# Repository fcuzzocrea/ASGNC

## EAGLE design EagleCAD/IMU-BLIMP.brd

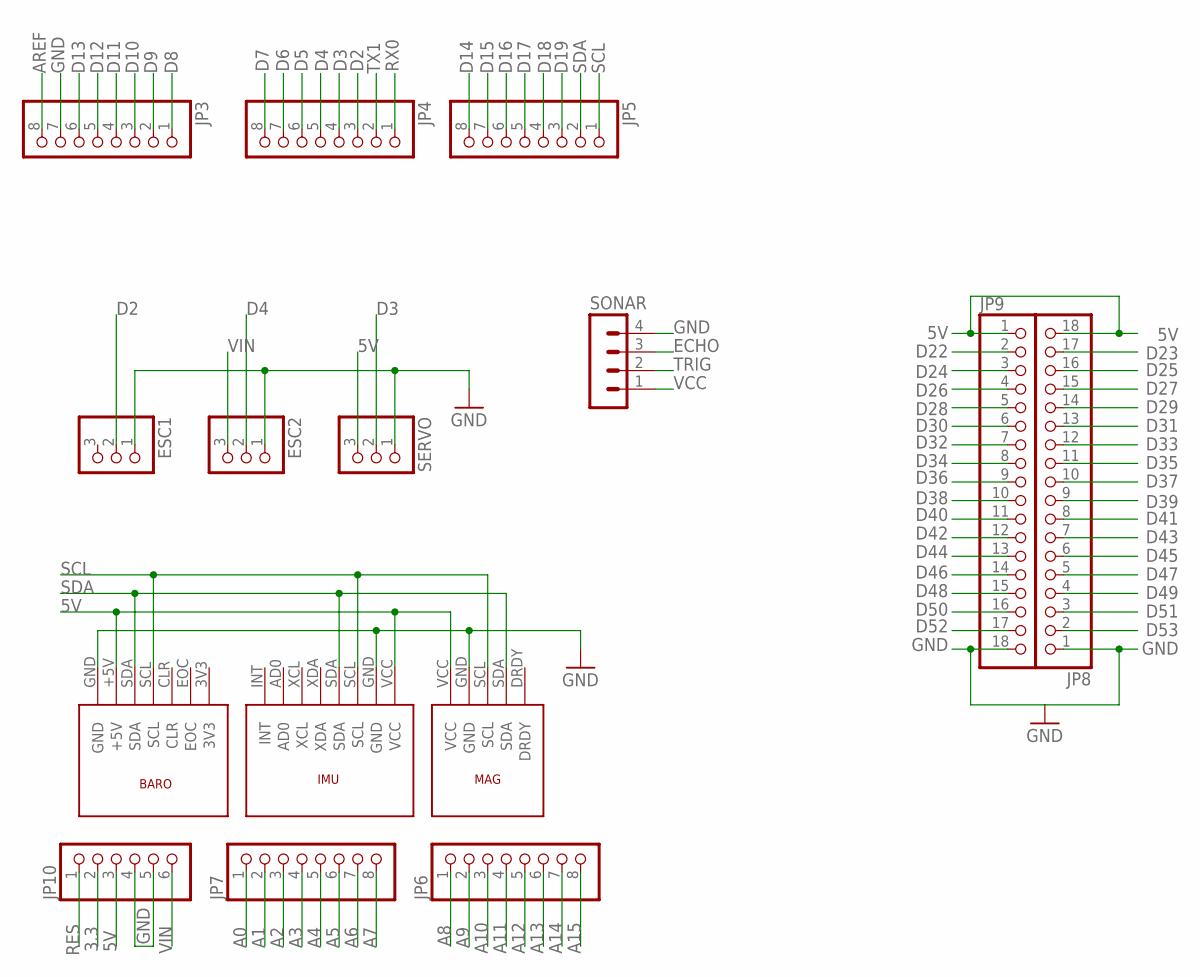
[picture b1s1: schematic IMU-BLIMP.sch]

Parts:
BARO1: BMP085
ESC1, ESC2: PINHD-1X3CB; 1X03-CLEANBIG
IMU1: MPU6050
JP3, JP4, JP5, JP6, JP7: PINHD-1X8CLEANBIG; 1X08-CLEANBIG
JP8, JP9: PINHD-1X18-BIG; 1X18-BIG
JP10: PINHD-1X6CB; 1X06-CLEANBIG
MAG1: HMC5883L
SERVO: PINHD-1X3CB; 1X03-CLEANBIG
SONAR: MA04-1

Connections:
3.3: JP10.2
5V: BARO1.+5V, IMU1.VCC, JP8.18, JP9.1, JP10.3, MAG1.VCC, SERVO.3, SONAR.1
A0: JP7.1
A1: JP7.2
A2: JP7.3
A3: JP7.4
A4: JP7.5
A5: JP7.6
A6: JP7.7
A7: JP7.8
A8: JP6.1
A9: JP6.2
A10: JP6.3
A11: JP6.4
A12: JP6.5
A13: JP6.6
A14: JP6.7
A15: JP6.8
AREF: JP3.8
D2: ESC1.2, JP4.3
D3: JP4.4, SERVO.2
D4: ESC2.2, JP4.5
D5: JP4.6, SONAR.3
D6: JP4.7, SONAR.2
D7: JP4.8
D8: JP3.1
D9: JP3.2
D10: JP3.3
D11: JP3.4
D12: JP3.5
D13: JP3.6
D14: JP5.8
D15: JP5.7
D16: JP5.6
D17: JP5.5
D18: JP5.4
D19: JP5.3
D22: JP9.2
D23: JP8.17
D24: JP9.3
D25: JP8.16
D26: JP9.4
D27: JP8.15
D28: JP9.5
D29: JP8.14
D30: JP9.6
D31: JP8.13
D32: JP9.7
D33: JP8.12
D34: JP9.8
D35: JP8.11
D36: JP9.9
D37: JP8.10
D38: JP9.10
D39: JP8.9
D40: JP9.11
D41: JP8.8
D42: JP9.12
D43: JP8.7
D44: JP9.13
D45: JP8.6
D46: JP9.14
D47: JP8.5
D48: JP9.15
D49: JP8.4
D50: JP9.16
D51: JP8.3
D52: JP9.17
D53: JP8.2
GND: BARO1.GND, ESC1.1, ESC2.1, IMU1.GND, JP3.7, JP8.1, JP9.18, JP10.4, JP10.5, MAG1.GND, SERVO.1, SONAR.4
RES: JP10.1
RX0: JP4.1
SCL: BARO1.SCL, IMU1.SCL, JP5.1, MAG1.SCL
SDA: BARO1.SDA, IMU1.SDA, JP5.2, MAG1.SDA
TX1: JP4.2
VIN: ESC2.3, JP10.6

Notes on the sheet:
SDA
SCL
GND
VCC
TRIG
ECHO
VIN

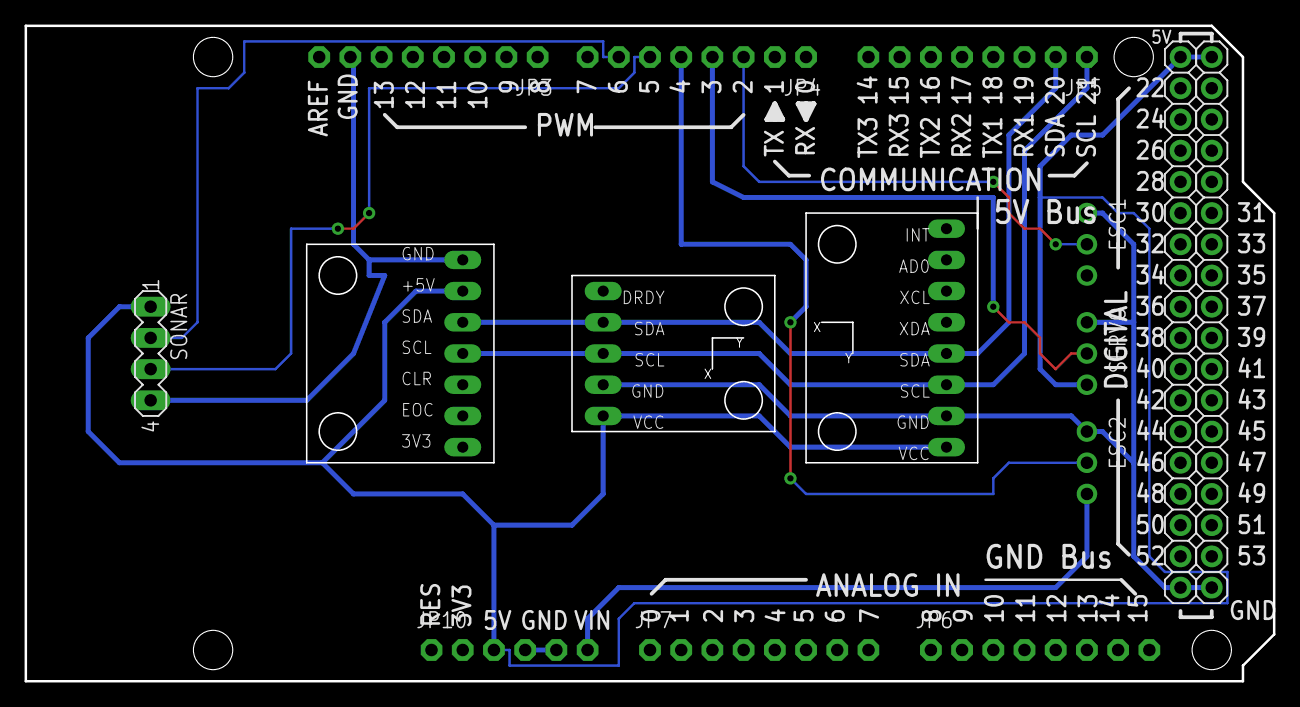
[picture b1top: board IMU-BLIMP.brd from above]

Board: 2 copper layers, 101.6 x 53.3 mm, 15 parts (0 on the bottom side), 10 nets.

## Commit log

2017-02-08 import from gdrive
